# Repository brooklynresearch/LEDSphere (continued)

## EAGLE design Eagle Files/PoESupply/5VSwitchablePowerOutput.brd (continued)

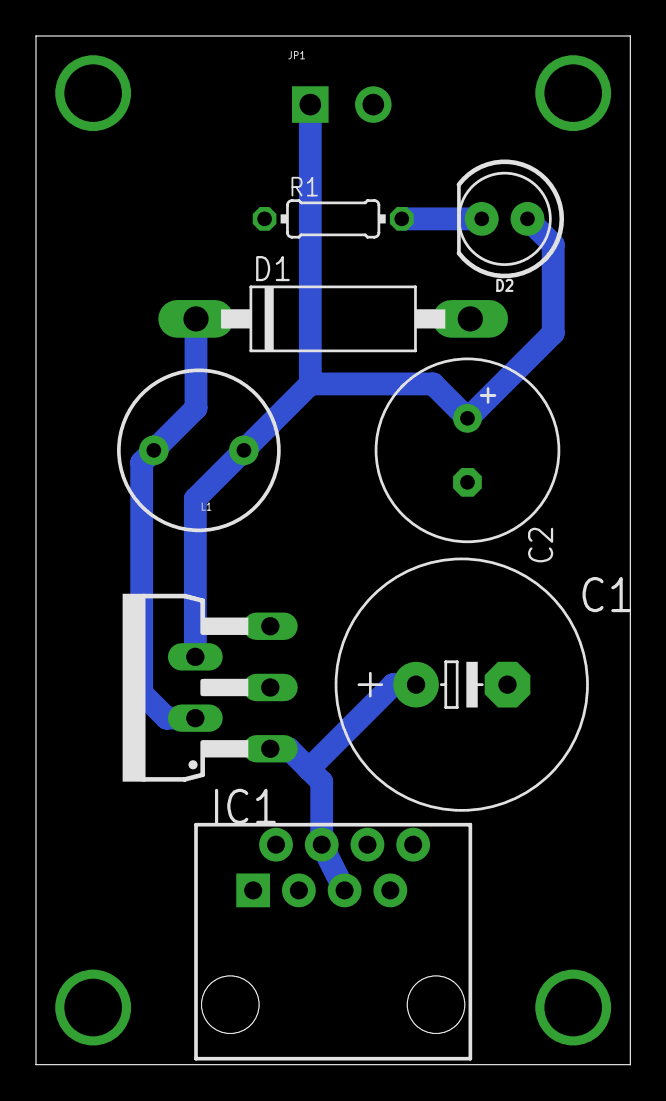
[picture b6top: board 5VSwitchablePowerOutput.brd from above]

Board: 2 copper layers, 33.0 x 57.1 mm, 9 parts (0 on the bottom side), 5 nets.

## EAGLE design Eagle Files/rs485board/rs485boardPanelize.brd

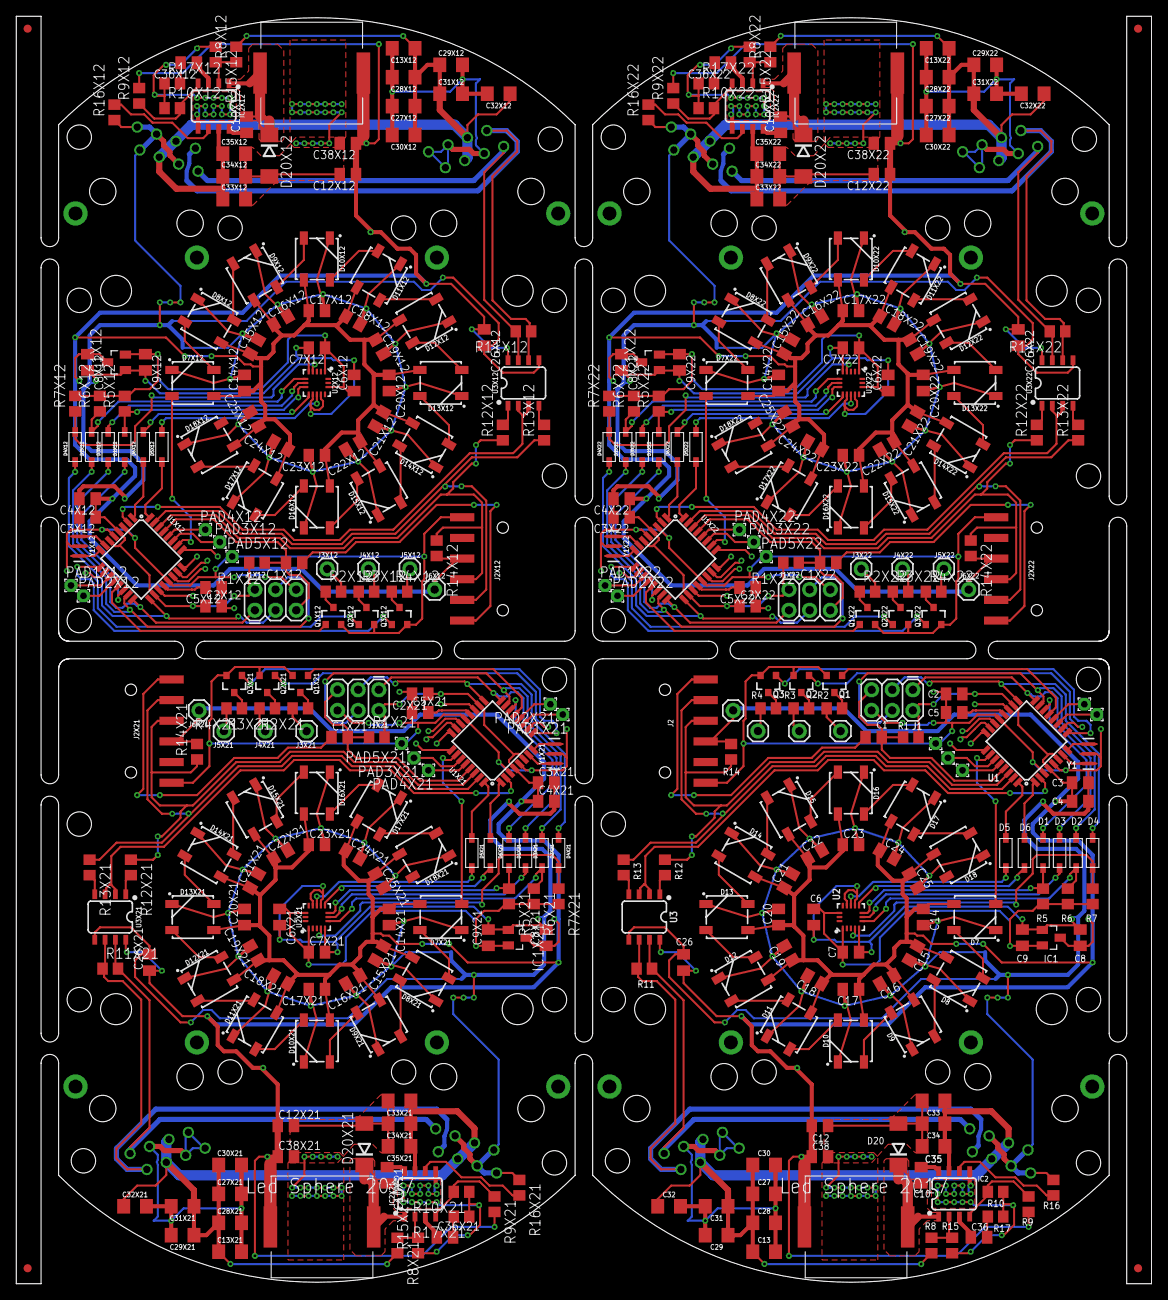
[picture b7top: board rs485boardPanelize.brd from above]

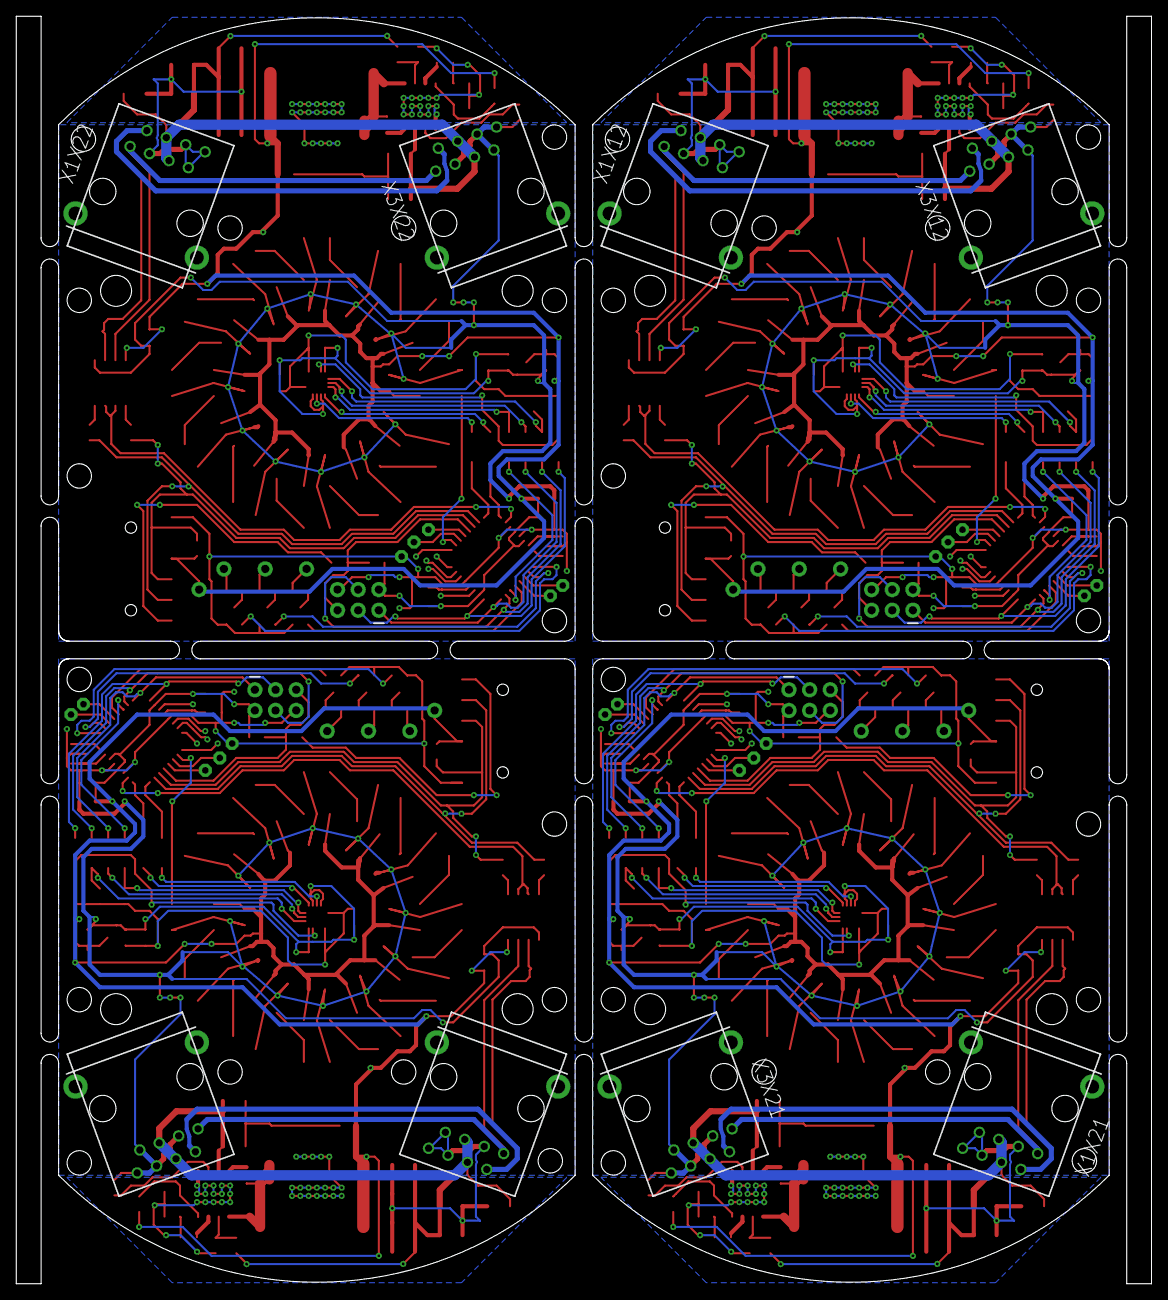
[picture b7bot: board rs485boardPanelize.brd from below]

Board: 2 copper layers, 139.6 x 155.8 mm, 384 parts (8 on the bottom side), 240 nets.

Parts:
C1, C1X12, C1X21, C1X22, C3, C3X12, C3X21, C3X22, C4, C4X12, C4X21, C4X22, C5, C5X12, C5X21, C5X22, C7, C7X12, C7X21, C7X22, C8, C8X12, C8X21, C8X22, C9, C9X12, C9X21, C9X22, C10, C10X12, C10X21, C10X22, C14, C14X12, C14X21, C14X22, C15, C15X12, C15X21, C15X22, C16, C16X12, C16X21, C16X22, C17, C17X12, C17X21, C17X22, C18, C18X12, C18X21, C18X22, C19, C19X12, C19X21, C19X22, C20, C20X12, C20X21, C20X22, C21, C21X12, C21X21, C21X22, C22, C22X12, C22X21, C22X22, C23, C23X12, C23X21, C23X22, C24, C24X12, C24X21, C24X22, C25, C25X12, C25X21, C25X22, C26, C26X12, C26X21, C26X22: 0.1uF; C0805K
C2, C2X12, C2X21, C2X22, C6, C6X12, C6X21, C6X22, C12, C12X12, C12X21, C12X22, C38, C38X12, C38X21, C38X22: 10uF; C0805K
C13, C13X12, C13X21, C13X22, C27, C27X12, C27X21, C27X22, C28, C28X12, C28X21, C28X22, C29, C29X12, C29X21, C29X22, C30, C30X12, C30X21, C30X22, C31, C31X12, C31X21, C31X22, C32, C32X12, C32X21, C32X22, C33, C33X12, C33X21, C33X22, C34, C34X12, C34X21, C34X22, C35, C35X12, C35X21, C35X22: 1uF 100V; 1206
C36, C36X12, C36X21, C36X22: 150pF; C0805K
D1, D1X12, D1X21, D1X22, D2, D2X12, D2X21, D2X22, D3, D3X12, D3X21, D3X22, D4, D4X12, D4X21, D4X22, D5, D5X12, D5X21, D5X22, D6, D6X12, D6X21, D6X22: 5819; SOD-123
D7, D7X12, D7X21, D7X22, D8, D8X12, D8X21, D8X22, D9, D9X12, D9X21, D9X22, D10, D10X12, D10X21, D10X22, D11, D11X12, D11X21, D11X22, D12, D12X12, D12X21, D12X22, D13, D13X12, D13X21, D13X22, D14, D14X12, D14X21, D14X22, D15, D15X12, D15X21, D15X22, D16, D16X12, D16X21, D16X22, D17, D17X12, D17X21, D17X22, D18, D18X12, D18X21, D18X22: WS2812B
D20, D20X12, D20X21, D20X22: B280-13-F; DO214AA
E$1, E$2, E$3, E$4: FIDUCIAL-1X2
IC1, IC1X12, IC1X21, IC1X22: XC6206P332MR; SOT23
IC2, IC2X12, IC2X21, IC2X22: MP2562; SO08
J1, J1X12, J1X21, J1X22: AVR_SPI_PROG_3X2PTH; 2X3
J2, J2X12, J2X21, J2X22: RA 6Pin SMD; 1X06-SMD_RA_MALE
J3, J3X12, J3X21, J3X22, J4, J4X12, J4X21, J4X22, J5, J5X12, J5X21, J5X22, J6, J6X12, J6X21, J6X22: 1X01
L1, L1X12, L1X21, L1X22: 15uH; SLF12575
PAD1, PAD1X12, PAD1X21, PAD1X22, PAD2, PAD2X12, PAD2X21, PAD2X22, PAD3, PAD3X12, PAD3X21, PAD3X22, PAD4, PAD4X12, PAD4X21, PAD4X22, PAD5, PAD5X12, PAD5X21, PAD5X22: 1,6/0,8
Q1, Q1X12, Q1X21, Q1X22, Q2, Q2X12, Q2X21, Q2X22, Q3, Q3X12, Q3X21, Q3X22: CJ3404; SOT23-3
R1, R1X12, R1X21, R1X22, R5, R5X12, R5X21, R5X22, R6, R6X12, R6X21, R6X22, R7, R7X12, R7X21, R7X22, R14, R14X12, R14X21, R14X22: 10K; R0805
R2, R2X12, R2X21, R2X22, R3, R3X12, R3X21, R3X22, R4, R4X12, R4X21, R4X22: DNP; R0805
R8, R8X12, R8X21, R8X22: 100K; R0805
R9, R9X12, R9X21, R9X22: 210K; R0805
R10, R10X12, R10X21, R10X22: 40.2k; R0805
R11, R11X12, R11X21, R11X22: 120; R0805
R12, R12X12, R12X21, R12X22, R13, R13X12, R13X21, R13X22: 1K; R0805
R15, R15X12, R15X21, R15X22: 17.4K; R0805
R16, R16X12, R16X21, R16X22: 200K; R0805
R17, R17X12, R17X21, R17X22: 158K; R0805
U1, U1X12, U1X21, U1X22: ATMEGA328P_TQFP; TQFP32-08
U2, U2X12, U2X21, U2X22: LIS3DH; LGA-16-3X3
U3, U3X12, U3X21, U3X22: SP485; SO08
X1, X1X12, X1X21, X1X22, X3, X3X12, X3X21, X3X22: RJ45-8P8C-8L-B; RJ45-SHIELD-DS1128-S80BP
Y1, Y1X12, Y1X21, Y1X22: 16MHz; RESONATOR-SMD-3.2X1.3

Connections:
+3V3: C6.1, C7.1, C9.1, IC1.2, R5.2, R6.2, R7.2, U2.1, U2.14
+3V3X12: C6X12.1, C7X12.1, C9X12.1, IC1X12.2, R5X12.2, R6X12.2, R7X12.2, U2X12.1, U2X12.14
+3V3X21: C6X21.1, C7X21.1, C9X21.1, IC1X21.2, R5X21.2, R6X21.2, R7X21.2, U2X21.1, U2X21.14
+3V3X22: C6X22.1, C7X22.1, C9X22.1, IC1X22.2, R5X22.2, R6X22.2, R7X22.2, U2X22.1, U2X22.14
+5V: C2.1, C3.1, C4.1, C8.1, C12.1, C14.1, C15.1, C16.1, C17.1, C18.1, C19.1, C20.1, C21.1, C22.1, C23.1, C24.1, C25.1, C26.1, C38.1, D7.1, D8.1, D9.1, D10.1, D11.1, D12.1, D13.1, D14.1, D15.1, D16.1, D17.1, D18.1, IC1.3, J1.2, J2.4, J6.1, L1.P$2, R1.2, R9.2, R14.2, U1.4, U1.6, U1.18, U3.8
+5VX12: C2X12.1, C3X12.1, C4X12.1, C8X12.1, C12X12.1, C14X12.1, C15X12.1, C16X12.1, C17X12.1, C18X12.1, C19X12.1, C20X12.1, C21X12.1, C22X12.1, C23X12.1, C24X12.1, C25X12.1, C26X12.1, C38X12.1, D7X12.1, D8X12.1, D9X12.1, D10X12.1, D11X12.1, D12X12.1, D13X12.1, D14X12.1, D15X12.1, D16X12.1, D17X12.1, D18X12.1, IC1X12.3, J1X12.2, J2X12.4, J6X12.1, L1X12.P$2, R1X12.2, R9X12.2, R14X12.2, U1X12.4, U1X12.6, U1X12.18, U3X12.8
+5VX21: C2X21.1, C3X21.1, C4X21.1, C8X21.1, C12X21.1, C14X21.1, C15X21.1, C16X21.1, C17X21.1, C18X21.1, C19X21.1, C20X21.1, C21X21.1, C22X21.1, C23X21.1, C24X21.1, C25X21.1, C26X21.1, C38X21.1, D7X21.1, D8X21.1, D9X21.1, D10X21.1, D11X21.1, D12X21.1, D13X21.1, D14X21.1, D15X21.1, D16X21.1, D17X21.1, D18X21.1, IC1X21.3, J1X21.2, J2X21.4, J6X21.1, L1X21.P$2, R1X21.2, R9X21.2, R14X21.2, U1X21.4, U1X21.6, U1X21.18, U3X21.8
+5VX22: C2X22.1, C3X22.1, C4X22.1, C8X22.1, C12X22.1, C14X22.1, C15X22.1, C16X22.1, C17X22.1, C18X22.1, C19X22.1, C20X22.1, C21X22.1, C22X22.1, C23X22.1, C24X22.1, C25X22.1, C26X22.1, C38X22.1, D7X22.1, D8X22.1, D9X22.1, D10X22.1, D11X22.1, D12X22.1, D13X22.1, D14X22.1, D15X22.1, D16X22.1, D17X22.1, D18X22.1, IC1X22.3, J1X22.2, J2X22.4, J6X22.1, L1X22.P$2, R1X22.2, R9X22.2, R14X22.2, U1X22.4, U1X22.6, U1X22.18, U3X22.8
+24V: C13.1, C27.1, C28.1, C29.1, C30.1, C31.1, C32.1, C33.1, C34.1, C35.1, IC2.7, R8.2, X1.4, X1.5, X3.4, X3.5
+24VX12: C13X12.1, C27X12.1, C28X12.1, C29X12.1, C30X12.1, C31X12.1, C32X12.1, C33X12.1, C34X12.1, C35X12.1, IC2X12.7, R8X12.2, X1X12.4, X1X12.5, X3X12.4, X3X12.5
+24VX21: C13X21.1, C27X21.1, C28X21.1, C29X21.1, C30X21.1, C31X21.1, C32X21.1, C33X21.1, C34X21.1, C35X21.1, IC2X21.7, R8X21.2, X1X21.4, X1X21.5, X3X21.4, X3X21.5
+24VX22: C13X22.1, C27X22.1, C28X22.1, C29X22.1, C30X22.1, C31X22.1, C32X22.1, C33X22.1, C34X22.1, C35X22.1, IC2X22.7, R8X22.2, X1X22.4, X1X22.5, X3X22.4, X3X22.5
A3: D7.4, U1.26
A3X12: D7X12.4, U1X12.26
A3X21: D7X21.4, U1X21.26
A3X22: D7X22.4, U1X22.26
A4: PAD3.1, U1.27
A4X12: PAD3X12.1, U1X12.27
A4X21: PAD3X21.1, U1X21.27
A4X22: PAD3X22.1, U1X22.27
A5: PAD4.1, U1.28
A5X12: PAD4X12.1, U1X12.28
A5X21: PAD4X21.1, U1X21.28
A5X22: PAD4X22.1, U1X22.28
AREF: C5.2, U1.20
AREFX12: C5X12.2, U1X12.20
AREFX21: C5X21.2, U1X21.20
AREFX22: C5X22.2, U1X22.20
BST: C10.1, IC2.8
BSTX12: C10X12.1, IC2X12.8
BSTX21: C10X21.1, IC2X21.8
BSTX22: C10X22.1, IC2X22.8
COMP: C36.1, IC2.3
COMPX12: C36X12.1, IC2X12.3
COMPX21: C36X21.1, IC2X21.3
COMPX22: C36X22.1, IC2X22.3
D2: D5.C, U1.32
D2X12: D5X12.C, U1X12.32
D2X21: D5X21.C, U1X21.32
D2X22: D5X22.C, U1X22.32
D3: D6.C, U1.1
D3X12: D6X12.C, U1X12.1
D3X21: D6X21.C, U1X21.1
D3X22: D6X22.C, U1X22.1
D5: Q3.1, U1.9
D5X12: Q3X12.1, U1X12.9
D5X21: Q3X21.1, U1X21.9
D5X22: Q3X22.1, U1X22.9
D6: Q2.1, U1.10
D6X12: Q2X12.1, U1X12.10
D6X21: Q2X21.1, U1X21.10
D6X22: Q2X22.1, U1X22.10
D7: PAD1.1, U1.11
D7X12: PAD1X12.1, U1X12.11
D7X21: PAD1X21.1, U1X21.11
D7X22: PAD1X22.1, U1X22.11
D8: PAD2.1, U1.12
D8X12: PAD2X12.1, U1X12.12
D8X21: PAD2X21.1, U1X21.12
D8X22: PAD2X22.1, U1X22.12
D9: Q1.1, U1.13
D9X12: Q1X12.1, U1X12.13
D9X21: Q1X21.1, U1X21.13
D9X22: Q1X22.1, U1X22.13
DIR: U1.2, U3.2, U3.3
DIRX12: U1X12.2, U3X12.2, U3X12.3
DIRX21: U1X21.2, U3X21.2, U3X21.3
DIRX22: U1X22.2, U3X22.2, U3X22.3
EN: IC2.2, R8.1, R15.2
ENX12: IC2X12.2, R8X12.1, R15X12.2
ENX21: IC2X21.2, R8X21.1, R15X21.2
ENX22: IC2X22.2, R8X22.1, R15X22.2
FB: IC2.4, R9.1, R10.2
FBX12: IC2X12.4, R9X12.1, R10X12.2
FBX21: IC2X21.4, R9X21.1, R10X21.2
FBX22: IC2X22.4, R9X22.1, R10X22.2
FREQ: IC2.6, R16.2
FREQX12: IC2X12.6, R16X12.2
FREQX21: IC2X21.6, R16X21.2
FREQX22: IC2X22.6, R16X22.2
GND: C2.2, C3.2, C4.2, C5.1, C6.2, C7.2, C8.2, C9.2, C12.2, C13.2, C14.2, C15.2, C16.2, C17.2, C18.2, C19.2, C20.2, C21.2, C22.2, C23.2, C24.2, C25.2, C26.2, C27.2, C28.2, C29.2, C30.2, C31.2, C32.2, C33.2, C34.2, C35.2, C38.2, D7.3, D8.3, D9.3, D10.3, D11.3, D12.3, D13.3, D14.3, D15.3, D16.3, D17.3, D18.3, D20.A, IC1.1, IC2.5, J1.6, J2.6, PAD5.1, Q1.2, Q2.2, Q3.2, R10.1, R15.1, R16.1, R17.1, U1.3, U1.5, U1.21, U2.5, U2.10, U2.12, U3.5, X1.3, X1.6, X1.7, X1.8, X3.3, X3.6, X3.7, X3.8, Y1.2
GNDX12: C2X12.2, C3X12.2, C4X12.2, C5X12.1, C6X12.2, C7X12.2, C8X12.2, C9X12.2, C12X12.2, C13X12.2, C14X12.2, C15X12.2, C16X12.2, C17X12.2, C18X12.2, C19X12.2, C20X12.2, C21X12.2, C22X12.2, C23X12.2, C24X12.2, C25X12.2, C26X12.2, C27X12.2, C28X12.2, C29X12.2, C30X12.2, C31X12.2, C32X12.2, C33X12.2, C34X12.2, C35X12.2, C38X12.2, D7X12.3, D8X12.3, D9X12.3, D10X12.3, D11X12.3, D12X12.3, D13X12.3, D14X12.3, D15X12.3, D16X12.3, D17X12.3, D18X12.3, D20X12.A, IC1X12.1, IC2X12.5, J1X12.6, J2X12.6, PAD5X12.1, Q1X12.2, Q2X12.2, Q3X12.2, R10X12.1, R15X12.1, R16X12.1, R17X12.1, U1X12.3, U1X12.5, U1X12.21, U2X12.5, U2X12.10, U2X12.12, U3X12.5, X1X12.3, X1X12.6, X1X12.7, X1X12.8, X3X12.3, X3X12.6, X3X12.7, X3X12.8, Y1X12.2
GNDX21: C2X21.2, C3X21.2, C4X21.2, C5X21.1, C6X21.2, C7X21.2, C8X21.2, C9X21.2, C12X21.2, C13X21.2, C14X21.2, C15X21.2, C16X21.2, C17X21.2, C18X21.2, C19X21.2, C20X21.2, C21X21.2, C22X21.2, C23X21.2, C24X21.2, C25X21.2, C26X21.2, C27X21.2, C28X21.2, C29X21.2, C30X21.2, C31X21.2, C32X21.2, C33X21.2, C34X21.2, C35X21.2, C38X21.2, D7X21.3, D8X21.3, D9X21.3, D10X21.3, D11X21.3, D12X21.3, D13X21.3, D14X21.3, D15X21.3, D16X21.3, D17X21.3, D18X21.3, D20X21.A, IC1X21.1, IC2X21.5, J1X21.6, J2X21.6, PAD5X21.1, Q1X21.2, Q2X21.2, Q3X21.2, R10X21.1, R15X21.1, R16X21.1, R17X21.1, U1X21.3, U1X21.5, U1X21.21, U2X21.5, U2X21.10, U2X21.12, U3X21.5, X1X21.3, X1X21.6, X1X21.7, X1X21.8, X3X21.3, X3X21.6, X3X21.7, X3X21.8, Y1X21.2
GNDX22: C2X22.2, C3X22.2, C4X22.2, C5X22.1, C6X22.2, C7X22.2, C8X22.2, C9X22.2, C12X22.2, C13X22.2, C14X22.2, C15X22.2, C16X22.2, C17X22.2, C18X22.2, C19X22.2, C20X22.2, C21X22.2, C22X22.2, C23X22.2, C24X22.2, C25X22.2, C26X22.2, C27X22.2, C28X22.2, C29X22.2, C30X22.2, C31X22.2, C32X22.2, C33X22.2, C34X22.2, C35X22.2, C38X22.2, D7X22.3, D8X22.3, D9X22.3, D10X22.3, D11X22.3, D12X22.3, D13X22.3, D14X22.3, D15X22.3, D16X22.3, D17X22.3, D18X22.3, D20X22.A, IC1X22.1, IC2X22.5, J1X22.6, J2X22.6, PAD5X22.1, Q1X22.2, Q2X22.2, Q3X22.2, R10X22.1, R15X22.1, R16X22.1, R17X22.1, U1X22.3, U1X22.5, U1X22.21, U2X22.5, U2X22.10, U2X22.12, U3X22.5, X1X22.3, X1X22.6, X1X22.7, X1X22.8, X3X22.3, X3X22.6, X3X22.7, X3X22.8, Y1X22.2
INT1: D5.A, U2.11
INT1X12: D5X12.A, U2X12.11
INT1X21: D5X21.A, U2X21.11
INT1X22: D5X22.A, U2X22.11
INT2: D6.A, U2.9
INT2X12: D6X12.A, U2X12.9
INT2X21: D6X21.A, U2X21.9
INT2X22: D6X22.A, U2X22.9
MISO: D3.C, J1.1, U1.16
MISOX12: D3X12.C, J1X12.1, U1X12.16
MISOX21: D3X21.C, J1X21.1, U1X21.16
MISOX22: D3X22.C, J1X22.1, U1X22.16
MISO_3.3V: D3.A, U2.7
MISO_3.3VX12: D3X12.A, U2X12.7
MISO_3.3VX21: D3X21.A, U2X21.7
MISO_3.3VX22: D3X22.A, U2X22.7
MOSI: D2.C, J1.4, U1.15
MOSIX12: D2X12.C, J1X12.4, U1X12.15
MOSIX21: D2X21.C, J1X21.4, U1X21.15
MOSIX22: D2X22.C, J1X22.4, U1X22.15
MOSI_3.3V: D2.A, R6.1, U2.6
MOSI_3.3VX12: D2X12.A, R6X12.1, U2X12.6
MOSI_3.3VX21: D2X21.A, R6X21.1, U2X21.6
MOSI_3.3VX22: D2X22.A, R6X22.1, U2X22.6
unnamed: Q1.3, R2.1
unnamed: Q1X12.3, R2X12.1
unnamed: Q1X21.3, R2X21.1
unnamed: Q1X22.3, R2X22.1
unnamed: D7.2, D8.4
unnamed: D7X12.2, D8X12.4
unnamed: D7X21.2, D8X21.4
unnamed: D7X22.2, D8X22.4
unnamed: D8.2, D9.4
unnamed: D8X12.2, D9X12.4
unnamed: D8X21.2, D9X21.4
unnamed: D8X22.2, D9X22.4
unnamed: J3.1, R2.2
unnamed: J3X12.1, R2X12.2
unnamed: J3X21.1, R2X21.2
unnamed: J3X22.1, R2X22.2
unnamed: Q2.3, R3.1
unnamed: Q2X12.3, R3X12.1
unnamed: Q2X21.3, R3X21.1
unnamed: Q2X22.3, R3X22.1
unnamed: J4.1, R3.2
unnamed: J4X12.1, R3X12.2
unnamed: J4X21.1, R3X21.2
unnamed: J4X22.1, R3X22.2
unnamed: Q3.3, R4.1
unnamed: Q3X12.3, R4X12.1
unnamed: Q3X21.3, R4X21.1
unnamed: Q3X22.3, R4X22.1
unnamed: J5.1, R4.2
unnamed: J5X12.1, R4X12.2
unnamed: J5X21.1, R4X21.2
unnamed: J5X22.1, R4X22.2
unnamed: D9.2, D10.4
unnamed: D9X12.2, D10X12.4
unnamed: D9X21.2, D10X21.4
unnamed: D9X22.2, D10X22.4
unnamed: D10.2, D11.4
unnamed: D10X12.2, D11X12.4
unnamed: D10X21.2, D11X21.4
unnamed: D10X22.2, D11X22.4
unnamed: D11.2, D12.4
unnamed: D11X12.2, D12X12.4
unnamed: D11X21.2, D12X21.4
unnamed: D11X22.2, D12X22.4
unnamed: D12.2, D13.4
unnamed: D12X12.2, D13X12.4
unnamed: D12X21.2, D13X21.4
unnamed: D12X22.2, D13X22.4
unnamed: D13.2, D14.4
unnamed: D13X12.2, D14X12.4
unnamed: D13X21.2, D14X21.4
unnamed: D13X22.2, D14X22.4
unnamed: D14.2, D15.4
unnamed: D14X12.2, D15X12.4
unnamed: D14X21.2, D15X21.4
unnamed: D14X22.2, D15X22.4
unnamed: D15.2, D16.4
unnamed: D15X12.2, D16X12.4
unnamed: D15X21.2, D16X21.4
unnamed: D15X22.2, D16X22.4
unnamed: D16.2, D17.4
unnamed: D16X12.2, D17X12.4
unnamed: D16X21.2, D17X21.4
unnamed: D16X22.2, D17X22.4
unnamed: D17.2, D18.4
unnamed: D17X12.2, D18X12.4
unnamed: D17X21.2, D18X21.4
unnamed: D17X22.2, D18X22.4
unnamed: C36.2, R17.2
unnamed: C36X12.2, R17X12.2
unnamed: C36X21.2, R17X21.2
unnamed: C36X22.2, R17X22.2
unnamed: R12.2, U3.1
unnamed: R12X12.2, U3X12.1
unnamed: R12X21.2, U3X21.1
unnamed: R12X22.2, U3X22.1
unnamed: R13.2, U3.4
unnamed: R13X12.2, U3X12.4
unnamed: R13X21.2, U3X21.4
unnamed: R13X22.2, U3X22.4
RESET: C1.2, J1.5, R1.1, U1.29
RESETX12: C1X12.2, J1X12.5, R1X12.1, U1X12.29
RESETX21: C1X21.2, J1X21.5, R1X21.1, U1X21.29
RESETX22: C1X22.2, J1X22.5, R1X22.1, U1X22.29
RESET_EXT: C1.1, J2.1
RESET_EXTX12: C1X12.1, J2X12.1
RESET_EXTX21: C1X21.1, J2X21.1
RESET_EXTX22: C1X22.1, J2X22.1
RS485A: R11.1, U3.6, X1.2, X3.2
RS485AX12: R11X12.1, U3X12.6, X1X12.2, X3X12.2
RS485AX21: R11X21.1, U3X21.6, X1X21.2, X3X21.2
RS485AX22: R11X22.1, U3X22.6, X1X22.2, X3X22.2
RS485B: R11.2, U3.7, X1.1, X3.1
RS485BX12: R11X12.2, U3X12.7, X1X12.1, X3X12.1
RS485BX21: R11X21.2, U3X21.7, X1X21.1, X3X21.1
RS485BX22: R11X22.2, U3X22.7, X1X22.1, X3X22.1
RX: J2.3, R12.1, R14.1, U1.30
RXX12: J2X12.3, R12X12.1, R14X12.1, U1X12.30
RXX21: J2X21.3, R12X21.1, R14X21.1, U1X21.30
RXX22: J2X22.3, R12X22.1, R14X22.1, U1X22.30
SCK: D4.C, J1.3, U1.17
SCKX12: D4X12.C, J1X12.3, U1X12.17
SCKX21: D4X21.C, J1X21.3, U1X21.17
SCKX22: D4X22.C, J1X22.3, U1X22.17
SCK_3.3V: D4.A, R7.1, U2.4
SCK_3.3VX12: D4X12.A, R7X12.1, U2X12.4
SCK_3.3VX21: D4X21.A, R7X21.1, U2X21.4
SCK_3.3VX22: D4X22.A, R7X22.1, U2X22.4
SS: D1.C, U1.14
SSX12: D1X12.C, U1X12.14
SSX21: D1X21.C, U1X21.14
SSX22: D1X22.C, U1X22.14
SS_3.3V: D1.A, R5.1, U2.8
SS_3.3VX12: D1X12.A, R5X12.1, U2X12.8
SS_3.3VX21: D1X21.A, R5X21.1, U2X21.8
SS_3.3VX22: D1X22.A, R5X22.1, U2X22.8
SW: C10.2, D20.C, IC2.1, L1.P$1
SWX12: C10X12.2, D20X12.C, IC2X12.1, L1X12.P$1
SWX21: C10X21.2, D20X21.C, IC2X21.1, L1X21.P$1
SWX22: C10X22.2, D20X22.C, IC2X22.1, L1X22.P$1
TX: J2.2, R13.1, U1.31
TXX12: J2X12.2, R13X12.1, U1X12.31
TXX21: J2X21.2, R13X21.1, U1X21.31
TXX22: J2X22.2, R13X22.1, U1X22.31
XTAL1: U1.7, Y1.1
XTAL1X12: U1X12.7, Y1X12.1
XTAL1X21: U1X21.7, Y1X21.1
XTAL1X22: U1X22.7, Y1X22.1
XTAL2: U1.8, Y1.3
XTAL2X12: U1X12.8, Y1X12.3
XTAL2X21: U1X21.8, Y1X21.3
XTAL2X22: U1X22.8, Y1X22.3

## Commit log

2017-12-21 Initial Commit
    Added all the current working files.
2017-12-21 Updated ReadMe
    Updated ReadMe Files
2017-12-23 add 1st version of file
2017-12-24 add more traces
2017-12-27 adjust wires
2017-12-27 add copper and text
2017-12-28 add values
2017-12-28 add value and gerber
2018-01-05 start coding
2018-01-05 functionalTestCode
2018-01-05 add processing
2018-01-06 add neopixel lib
2018-01-06 add test pattern
2018-01-07 add id for back response
2018-01-07 add envelop
2018-01-07 add slider
2018-01-07 add threshold slider
2018-01-07 add hysteresis
2018-01-08 add support file
2018-01-08 add threshold on stableness
2018-01-08 add center
2018-01-08 add parameter setting
2018-01-08 add another control code
2018-01-08 fix bug
2018-01-09 temp bug walk around
2018-01-09 adaptor board
2018-01-09 add gerber
2018-01-16 add note
2018-01-16 add 10 address
2018-01-16 update code
2018-03-04 test speed
2018-03-12 add latency Test
2018-03-12 remove return
2018-03-12 kind of work
2018-03-12 mills work
2018-03-12 make it fast
2018-03-13 code working with high speed
2018-03-15 add adjusting
2018-03-15 add lost detection
2018-03-15 inc brightness
2018-03-15 add resistor
2018-03-15 back up
2018-03-16 48V upgrade
2018-04-02 Prototype Demo Code
    Processing demo code for the initial prototype.
2018-04-04 add ulp tool
    Example: add attribute of LIS3DH
    run select7 -cv * : LIS3DH
    run attrib-add108
2018-04-04 add lcsc part number
2018-04-26 add some reference
2018-04-26 duplicate board and try array_board ulp
2018-04-26 remove copper fill on 5V
2018-04-26 ready to panelize
2018-04-27 adjust spacing
2018-04-27 clean up 2*2
2018-04-27 move to AB 2*2
2018-04-27 panel finish, need add fiducial
2018-04-27 add fiducial
2018-04-27 reduce tab size
2018-04-27 fix text
2018-04-27 export gerber
2018-05-07 start working on BOM
2018-05-07 finish bom
2018-05-07 add smt file
2018-05-07 add adaptor board
2018-05-17 add ID back
2018-05-17 start to work
2018-05-17 add delay on serial open
2018-05-17 lots units kind of work
2018-05-18 add calibration
2018-05-23 copy bootloader with eeprom support from penis wall project
2018-05-23 add neopixel support for testing
2018-05-23 add mac script to upload bootloader
2018-05-23 add mac script to update eeprom
2018-05-23 add angle representation with arc
2018-06-09 update power on pattern
2018-06-09 add fade feature
2018-06-11 add burn batch file
2018-06-12 update UI for 200 balls
2018-06-12 add id beside controller
2018-06-13 add boards
2018-08-18 update layout
2018-08-31 Fix empty bug
2018-08-31 add compile time
2018-08-31 update controller ID limit
2018-08-31 fix send offset wrong loop bug
2018-08-31 remove position print
2018-08-31 add color var
2018-09-01 increase refresh rate, add override mode
2018-09-01 fix long buffer fail bug
2018-09-01 update hex
2018-09-04 start working on auto reset of Leonardo
2018-09-04 add marco for auto reset
2018-09-04 fix CDC mess with WDT
2018-09-04 disable error print
2018-09-04 add test LED code
2018-09-04 update logic for testing
2018-09-05 remove overide
2018-09-05 reduce hotplug check frequecy
2018-09-05 optimize code to reduce time on drawing
2018-09-05 count time when board connects
2018-09-05 fix fast packet lost issue
2018-09-05 add timer for performance
2018-09-05 remove additional buffer as Arduino can buf
2018-09-05 add basic ripple
2018-09-05 add ripple color defination
2018-09-05 add wave effect
2018-09-05 add breath effect
2018-09-12 add 3d model to help solder
2018-09-12 update size
2018-09-12 edit work on pi
2018-09-22 change firmware
2018-09-22 add auto-reconnect python to check board ID
2018-09-23 add code to program controller
2018-09-23 add reading code
2018-10-02 add top bottom mirror
2018-10-02 change object pos and display pos
2018-10-02 use absolute path for python
2018-10-02 add tilt color
2019-04-30 auto reset is getting problem
2019-05-01 add osc
2019-05-02 update circle
2019-05-02 adjust threshold
2019-05-02 edit effect, add reset command
